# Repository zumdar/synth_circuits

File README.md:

# synth_circuits
synthesizer and audio circuits

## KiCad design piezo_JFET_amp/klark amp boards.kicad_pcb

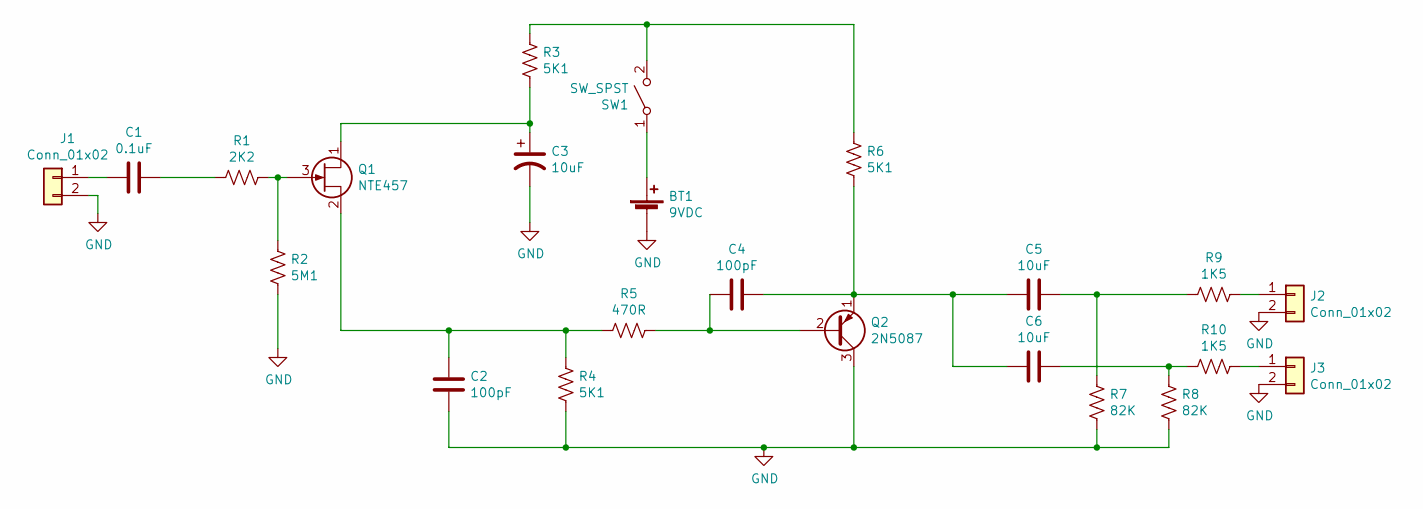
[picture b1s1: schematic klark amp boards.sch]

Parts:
BT1: 9VDC; 2_pin_wire_in
C1: 0.1uF; C_Disc_D5.0mm_W2.5mm_P5.00mm
C2, C4: 100pF; C_Disc_D5.0mm_W2.5mm_P5.00mm
C3: 10uF; CP_Radial_D8.0mm_P3.50mm
C5, C6: 10uF; CP_Radial_D8.0mm_P5.00mm
J1, J2, J3: Conn_01x02; 2_pin_wire_in
Q1: NTE457; TO-92L_Inline_Wide
Q2: 2N5087; TO-92_Inline_Wide
R1: 2K2; R_Axial_DIN0207_L6.3mm_D2.5mm_P10.16mm_Horizontal
R2: 5M1; R_Axial_DIN0207_L6.3mm_D2.5mm_P10.16mm_Horizontal
R3, R4, R6: 5K1; R_Axial_DIN0207_L6.3mm_D2.5mm_P10.16mm_Horizontal
R5: 470R; R_Axial_DIN0207_L6.3mm_D2.5mm_P10.16mm_Horizontal
R7, R8: 82K; R_Axial_DIN0207_L6.3mm_D2.5mm_P10.16mm_Horizontal
R9, R10: 1K5; R_Axial_DIN0207_L6.3mm_D2.5mm_P10.16mm_Horizontal
SW1: SW_SPST; SPST_10TC605

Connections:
GND: BT1.2 (-), C2.1, C3.2, J1.2, J2.2, J3.2, Q2.3 (C), R2.1, R4.1, R7.2, R8.2
unnamed: BT1.1 (+), SW1.1 (A)
unnamed: C1.1, R1.2
unnamed: C1.2, J1.1
unnamed: C2.2, Q1.2 (S), R4.2, R5.1
unnamed: C3.1, Q1.1 (D), R3.1
unnamed: C4.1, Q2.2 (B), R5.2
unnamed: C4.2, C5.1, C6.1, Q2.1 (E), R6.1
unnamed: C5.2, R7.1, R9.2
unnamed: C6.2, R8.1, R10.2
unnamed: J2.1, R9.1
unnamed: J3.1, R10.1
unnamed: Q1.3 (G), R1.1, R2.2
unnamed: R3.2, R6.2, SW1.2 (B)

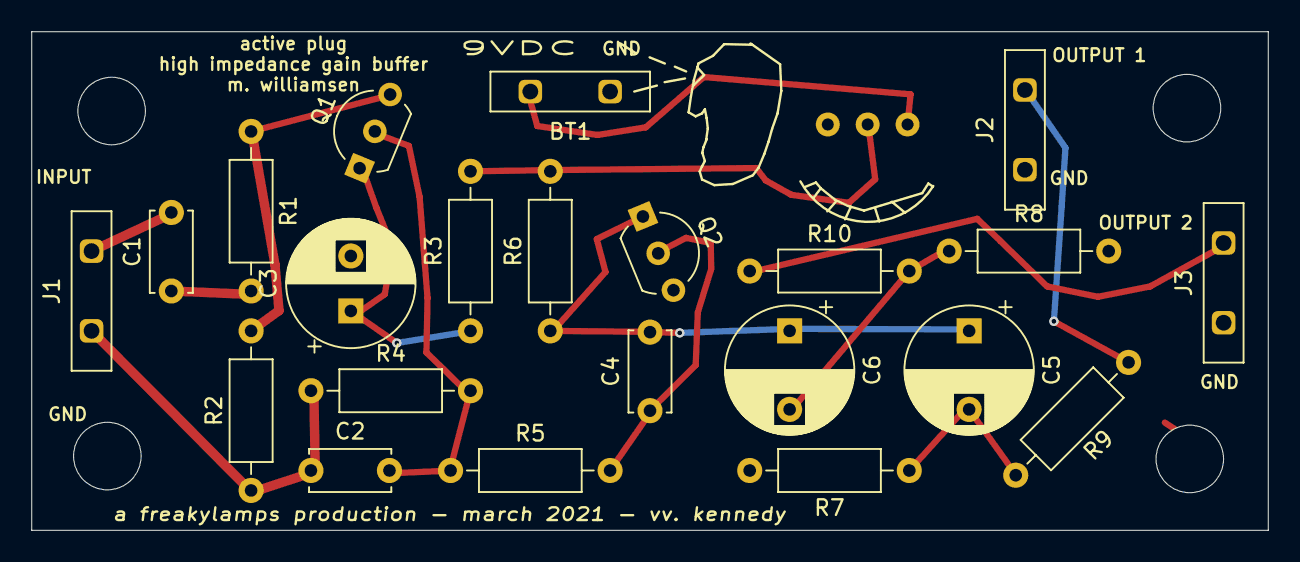
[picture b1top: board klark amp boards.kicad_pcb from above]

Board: 4 copper layers, 78.7 x 31.8 mm, 23 parts (1 on the bottom side), 14 nets.

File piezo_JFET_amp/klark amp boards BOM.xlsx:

Id | Designator | Package | Quantity | Designation
1 | Q2 | TO-92_Inline_Wide | 1 | 2N5087
2 | Q1 | TO-92L_Inline_Wide | 1 | NTE457
6 | BT1 | 2_pin_wire_in | 1 | 9VDC
7 | SW1 | SPST_10TC605 | 1 | SW_SPST
8 | R10,R9 | R_Axial_DIN0207_L6.3mm_D2.5mm_P10.16mm_Horizontal | 2 | 1K5
9 | R8,R7 | R_Axial_DIN0207_L6.3mm_D2.5mm_P10.16mm_Horizontal | 2 | 82K
10 | R6,R4,R3 | R_Axial_DIN0207_L6.3mm_D2.5mm_P10.16mm_Horizontal | 3 | 5K1
11 | R5 | R_Axial_DIN0207_L6.3mm_D2.5mm_P10.16mm_Horizontal | 1 | 470R
12 | R2 | R_Axial_DIN0207_L6.3mm_D2.5mm_P10.16mm_Horizontal | 1 | 5M1
13 | R1 | R_Axial_DIN0207_L6.3mm_D2.5mm_P10.16mm_Horizontal | 1 | 2K2
14 | C6,C5 | CP_Radial_D8.0mm_P5.00mm | 2 | 10uF
15 | C4,C2 | C_Disc_D5.0mm_W2.5mm_P5.00mm | 2 | 100pF
16 | C3 | CP_Radial_D8.0mm_P3.50mm | 1 | 10uF
17 | C1 | C_Disc_D5.0mm_W2.5mm_P5.00mm | 1 | 0.1uF

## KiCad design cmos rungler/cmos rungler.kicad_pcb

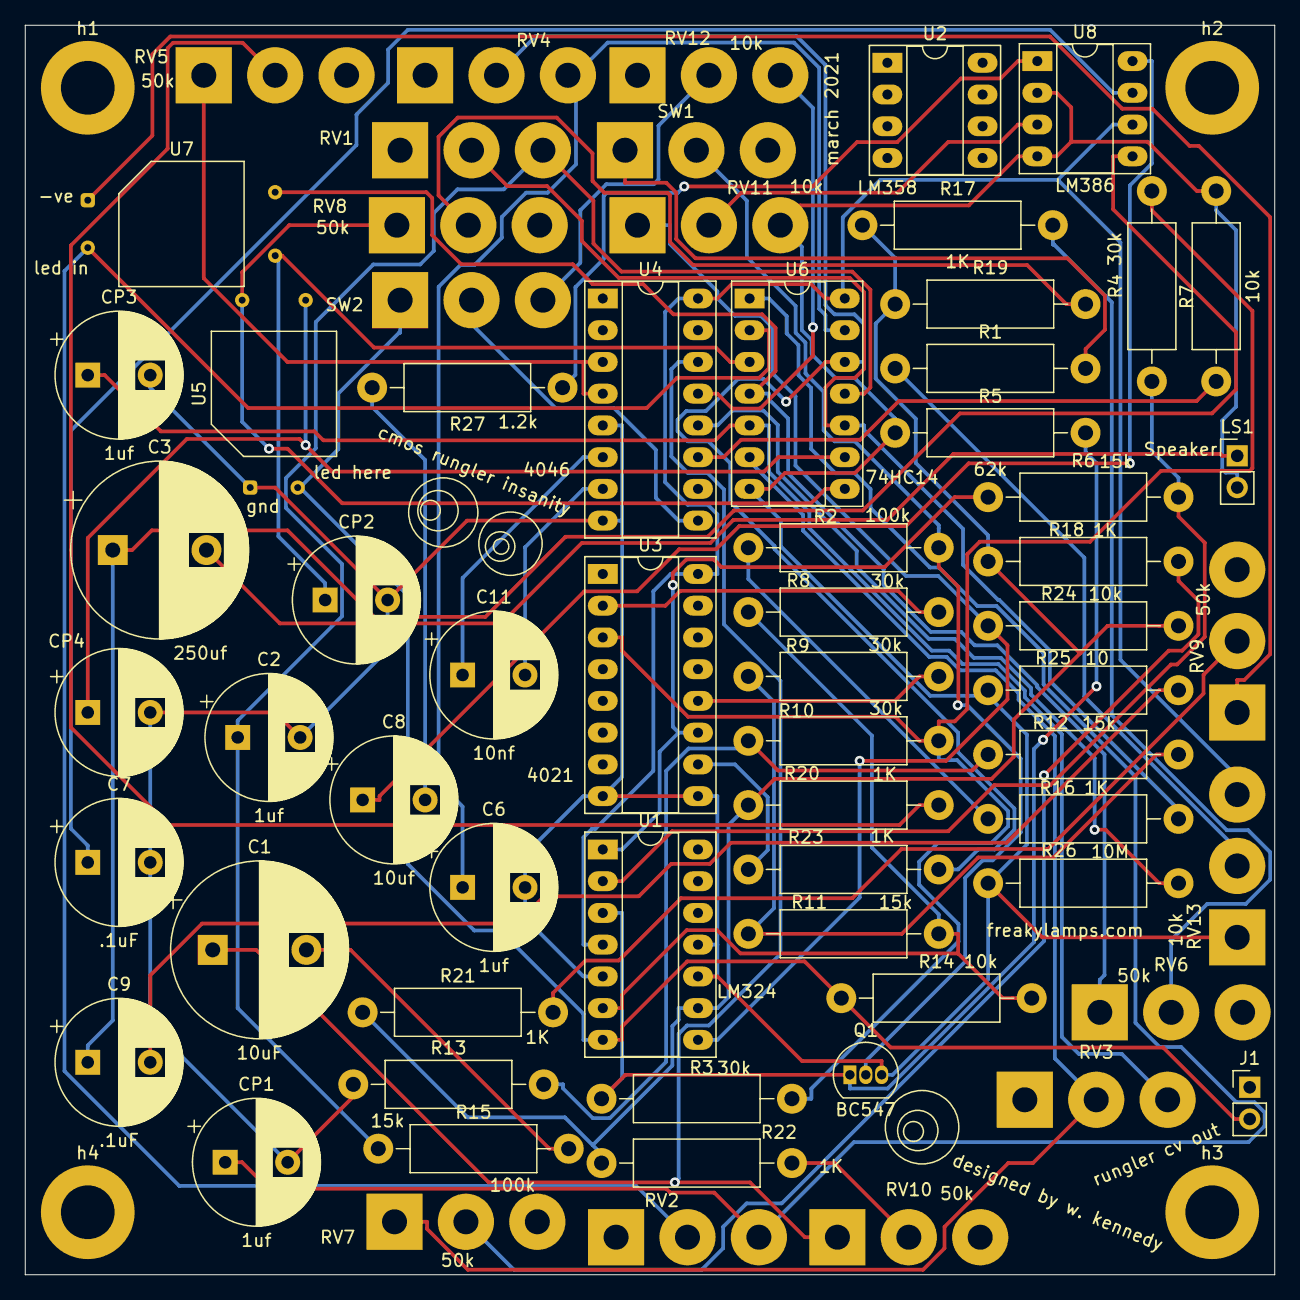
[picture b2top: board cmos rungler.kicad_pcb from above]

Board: 2 copper layers, 100.0 x 100.0 mm, 69 parts (0 on the bottom side), 56 nets.

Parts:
C1: 10uF; CP_Radial_D14.0mm_P7.50mm
C2, C6: 1uf; CP_Radial_D10.0mm_P5.00mm
C3: 250uf; CP_Radial_D14.0mm_P7.50mm
C7, C9: .1uF; CP_Radial_D10.0mm_P5.00mm
C8: 10uf; CP_Radial_D10.0mm_P5.00mm
C11: 10nf; CP_Radial_D10.0mm_P5.00mm
CP1, CP3: 1uf; CP_Radial_D10.0mm_P5.00mm
CP2, CP4: C; CP_Radial_D10.0mm_P5.00mm
J1: Conn_01x02_Male; PinHeader_1x02_P2.54mm_Vertical
LS1: Speaker; PinHeader_1x02_P2.54mm_Vertical
Q1: BC547; TO-92_Inline
R1, R5: 62k; R_Axial_DIN0411_L9.9mm_D3.6mm_P15.24mm_Horizontal
R2, R15: 100k; R_Axial_DIN0411_L9.9mm_D3.6mm_P15.24mm_Horizontal
R3, R4, R8, R9, R10: 30k; R_Axial_DIN0411_L9.9mm_D3.6mm_P15.24mm_Horizontal
R6, R11, R12, R13: 15k; R_Axial_DIN0411_L9.9mm_D3.6mm_P15.24mm_Horizontal
R7, R14, R24: 10k; R_Axial_DIN0411_L9.9mm_D3.6mm_P15.24mm_Horizontal
R16, R17, R18, R19, R20, R21, R22, R23: 1K; R_Axial_DIN0411_L9.9mm_D3.6mm_P15.24mm_Horizontal
R25: 10; R_Axial_DIN0411_L9.9mm_D3.6mm_P15.24mm_Horizontal
R26: 10M; R_Axial_DIN0411_L9.9mm_D3.6mm_P15.24mm_Horizontal
R27: 1.2k; R_Axial_DIN0411_L9.9mm_D3.6mm_P15.24mm_Horizontal
RV1, RV11, RV12, RV13: 10k; SolderWirePad_1x03_P5.715mm_Drill2mm
RV2, RV3, RV4: R_POT_US; SolderWirePad_1x03_P5.715mm_Drill2mm
RV5, RV6, RV7, RV8, RV9, RV10: 50k; SolderWirePad_1x03_P5.715mm_Drill2mm
SW1, SW2: SW_SPDT; SolderWirePad_1x03_P5.715mm_Drill2mm
U1: LM324; DIP-14_W7.62mm_Socket_LongPads
U2: LM358; DIP-8_W7.62mm_Socket_LongPads
U3: 4021; DIP-16_W7.62mm_Socket_LongPads
U4: 4046; DIP-16_W7.62mm_Socket_LongPads
U5, U7: VTL5C; PerkinElmer_VTL5C
U6: 74HC14; DIP-14_W7.62mm_Socket_LongPads
U8: LM386; DIP-8_W7.62mm_Socket_LongPads
h1, h2, h3, h4: MountingHole_4.3mm_M4_DIN965_Pad

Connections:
+12V: RV13.3, U1.4, U3.16, U4.16, U6.14, U8.6
CLK: R23.1, U3.10
GND: C2.2, C6.2, C7.2, CP1.2, CP2.2, CP3.2, CP4.2, LS1.2, Q1.3, R5.1, R7.2, R13.1, R25.1, R26.1, RV11.3, RV13.1, U1.5, U1.10, U1.11, U3.8, U3.9, U4.5, U4.8, U5.1, U6.7, U8.2, U8.4
unnamed: C1.2, R15.2
unnamed: C2.1, R15.1, RV1.3, U6.11
unnamed: C3.1, C9.1, U8.5
unnamed: C3.2, LS1.1
unnamed: C6.1, RV4.3, U6.13
unnamed: C7.1, U8.7
unnamed: C8.1, U8.8
unnamed: C8.2, R27.2
unnamed: C9.2, R25.2
unnamed: C11.1, U4.6
unnamed: C11.2, U4.7
unnamed: CP1.1, RV2.3, U6.1
unnamed: CP2.1, U6.3, U7.4
unnamed: CP3.1, RV3.3, U6.5
unnamed: CP4.1, U5.4, U6.9
unnamed: Q1.1, R3.1, R5.2, U1.3
unnamed: Q1.2, R2.2, SW1.2
unnamed: R1.1, RV13.2
unnamed: R1.2, SW1.1
unnamed: R4.1, R6.2, U1.2
unnamed: R6.1, U1.1, U3.11
unnamed: R7.1, U4.11
unnamed: R8.2, U3.2
unnamed: R9.2, U3.12
unnamed: R10.1, R12.1, R13.2
unnamed: R3.2, R4.2, R10.2, U3.3
unnamed: R9.1, R11.1, R12.2
unnamed: R8.1, R11.2, R14.2, U1.6
unnamed: R16.2, RV1.2, U6.10
unnamed: R17.1, R18.1, R19.1, R20.1, R21.1, R22.1, R24.2, U1.9
unnamed: R17.2, RV6.2
unnamed: R18.2, RV7.2
unnamed: R19.2, RV8.2
unnamed: R20.2, RV5.2
unnamed: R21.2, RV9.2
unnamed: R22.2, RV10.2
unnamed: R23.2, RV4.2, U6.12
unnamed: R24.1, RV11.1, U1.8
unnamed: R26.2, U4.12
unnamed: R27.1, U8.1
unnamed: RV3.2, RV7.1, U6.6
unnamed: RV6.1, U6.4, U7.3
unnamed: RV8.1, U5.3, U6.8
unnamed: RV9.1, U7.1
unnamed: RV11.2, U8.3
unnamed: RV12.2, SW2.3
unnamed: RV12.3, U4.13
unnamed: SW2.2, U4.9
VCOout: RV5.1, U4.3, U4.4
ledin: RV2.2, U6.2, U7.2
rungCLK2: R2.1, R16.1
rungCV: J1.2, R14.1, SW2.1, U1.7, U5.2
triangleCLK2: C1.1, RV10.1, U4.14

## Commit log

2021-05-31 cmos and serge vco upload
2021-05-31 cleaning up
2021-06-02 adding pdf sch and pcb for rungler
2021-06-03 adding piezo amp
